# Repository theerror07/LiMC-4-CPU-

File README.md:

# LiMC-4-CPU-
All the documentation and information about my CPU project.

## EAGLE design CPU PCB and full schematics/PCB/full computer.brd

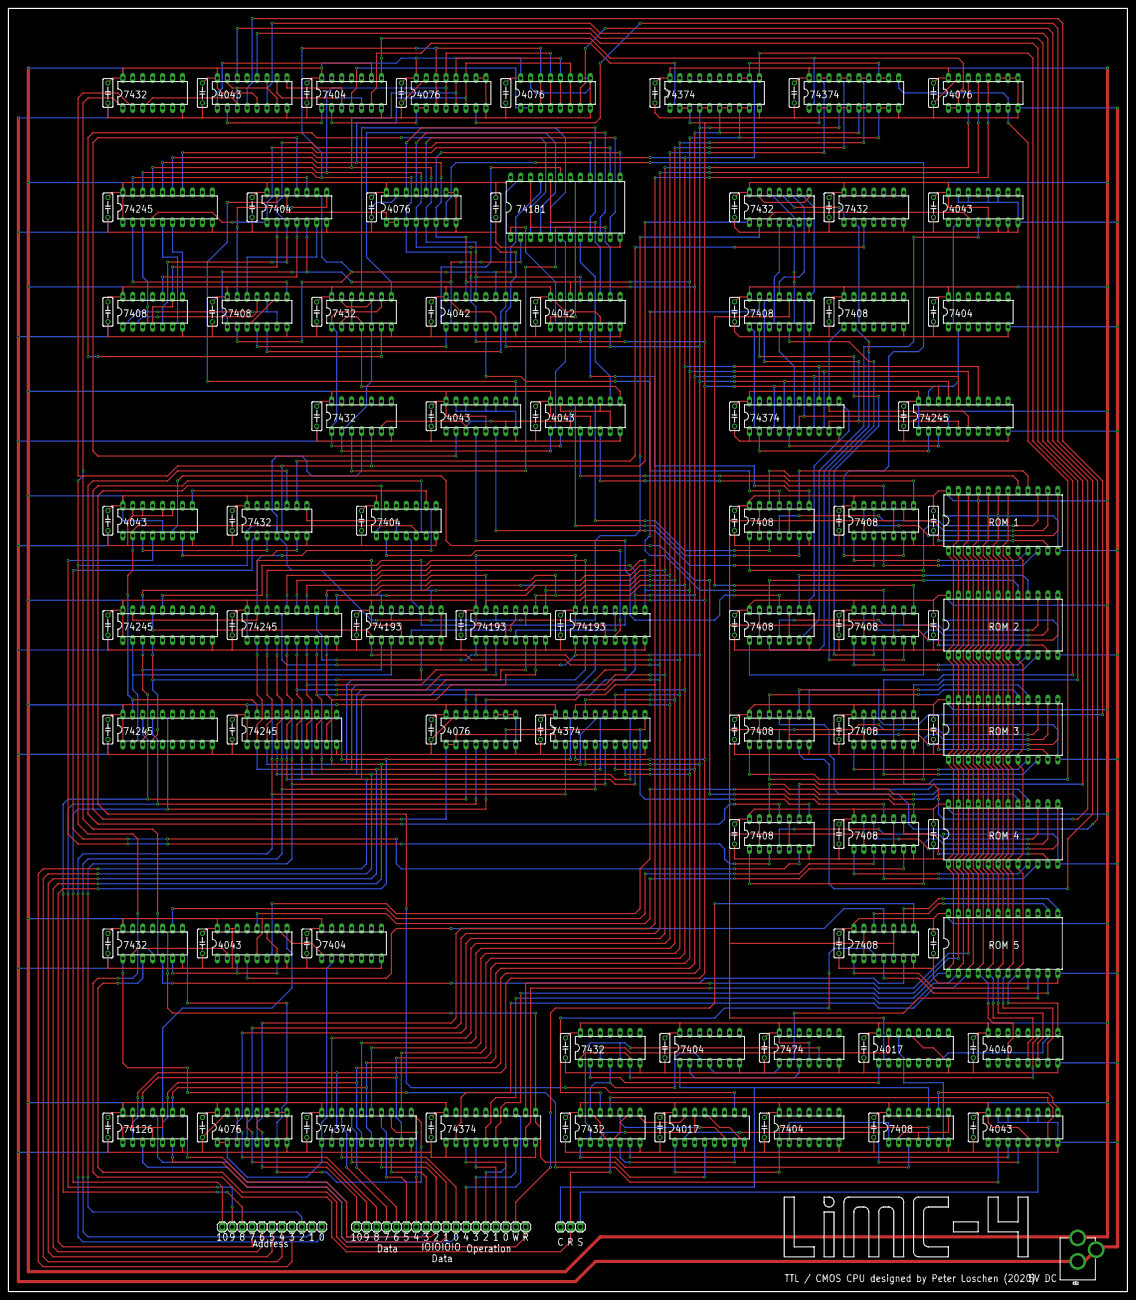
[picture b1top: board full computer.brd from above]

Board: 2 copper layers, 285.8 x 327.7 mm, 146 parts (0 on the bottom side), 244 nets.

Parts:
E$1, E$3, E$4, E$5, E$6, E$7, E$8, E$9, E$10, E$11, E$12, E$13, E$14, E$15, E$16, E$17, E$18, E$19, E$20, E$21, E$22, E$23, E$24, E$25, E$26, E$27, E$28, E$29, E$30, E$31, E$32, E$33, E$34, E$35, E$36, E$37, E$38, E$39, E$40, E$41, E$42, E$43, E$44, E$45, E$46, E$47, E$48, E$49, E$50, E$51, E$52, E$53, E$54, E$55, E$56, E$57, E$58, E$59, E$60, E$61, E$62, E$63, E$64, E$65, E$66, E$67, E$68, E$69, E$70, E$71, E$72: C050-025X075
E$2: POWER_JACK_PTH
IC1, IC7: 4017N; DIL16
IC2, IC27, IC34, IC48, IC49, IC56, IC61: 4043N; DIL16
IC3, IC8, IC26, IC40, IC44, IC45, IC55, IC59, IC62: 74LS32N; DIL14
IC4, IC16, IC17, IC18, IC19, IC20, IC21, IC22, IC23, IC24, IC51, IC52, IC53, IC54: 74ALS08N; DIL14
IC5, IC10, IC31, IC39, IC46, IC57, IC68: 74ALS04N; DIL14
IC6: 4040N; DIL16
IC9: 74LS74N; DIL14
IC11, IC12, IC13, IC14, IC15: 28C16AP; DIL24-6
IC25, IC38, IC50, IC63, IC64, IC67: 4076N; DIL16
IC28, IC29, IC37, IC60, IC65, IC66: 74LS374N; DIL20
IC30: 74LS126N; DIL14
IC32, IC33, IC35, IC36, IC47, IC58: 74LS245N; DIL20
IC41: 74S181N; DIL24-6
IC42, IC43: 4042N; DIL16
JP1: 1X03
JP2: 1X18
JP3: 1X11
V1, V2, V3: 74193N; DIL16

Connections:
ACCUMULATORLATCH: IC16.6, IC50.7
ACCUMULATOROUTPUT: IC16.3, IC49.6
ADDRESS0: IC35.18, IC37.2, JP3.1
ADDRESS1: IC35.17, IC37.5, JP3.2
ADDRESS2: IC35.16, IC37.6, JP3.3
ADDRESS3: IC35.15, IC37.9, JP3.4
ADDRESS4: IC35.14, IC37.12, JP3.5
ADDRESS5: IC35.13, IC37.15, JP3.6
ADDRESS6: IC35.12, IC37.16, JP3.7
ADDRESS7: IC35.11, IC37.19, JP3.8
ADDRESS8: IC36.18, IC38.3, JP3.9
ADDRESS9: IC36.17, IC38.4, JP3.10
ADDRESS10: IC36.16, IC38.5, JP3.11
ALUFLAGOUT: IC19.11, IC49.4
BUFFERTODATABUS: IC22.6, IC27.12
CUREAD: IC2.2, IC26.1
D0: IC28.3, IC30.3, JP2.8
D1: IC28.4, IC30.6, JP2.9
D2: IC28.7, IC30.8, JP2.10
D3: IC28.8, IC30.11, JP2.11
D4: IC28.13, JP2.12
D5: IC28.14, JP2.13
D6: IC28.17, JP2.14
D7: IC28.18, JP2.15
D8: IC25.14, JP2.16
D9: IC25.13, JP2.17
D10: IC25.12, JP2.18
DATABUS0: IC28.2, IC30.2, IC32.18, IC37.3, IC42.4, IC43.4, IC47.18, IC50.3, IC58.18, IC60.3, IC63.3, IC63.14, IC64.3, IC64.14, IC65.2, IC65.3, IC66.2, IC66.3, V1.15
DATABUS1: IC28.5, IC30.5, IC32.17, IC37.4, IC42.7, IC43.7, IC47.17, IC50.4, IC58.17, IC60.4, IC63.4, IC63.13, IC64.4, IC64.13, IC65.4, IC65.5, IC66.4, IC66.5, V1.1
DATABUS2: IC28.6, IC30.9, IC32.16, IC37.7, IC42.13, IC43.13, IC47.16, IC50.5, IC58.16, IC60.7, IC63.5, IC63.12, IC64.5, IC64.12, IC65.6, IC65.7, IC66.6, IC66.7, V1.10
DATABUS3: IC28.9, IC30.12, IC32.15, IC37.8, IC42.14, IC43.14, IC47.15, IC50.6, IC58.15, IC60.8, IC63.6, IC63.11, IC64.6, IC64.11, IC65.8, IC65.9, IC66.8, IC66.9, V1.9
DATABUS4: IC28.12, IC32.14, IC37.13, IC47.14, IC58.14, IC60.13, IC65.12, IC65.13, IC66.12, IC66.13, V2.15
DATABUS5: IC28.15, IC32.13, IC37.14, IC66.14, IC66.15, V2.1
DATABUS6: IC28.16, IC32.12, IC37.17, IC66.16, IC66.17, V2.10
DATABUS7: IC28.19, IC32.11, IC37.18, IC66.18, IC66.19, V2.9
DATABUS8: IC25.3, IC33.18, IC38.14, IC67.3, IC67.14, V3.15
DATABUS9: IC25.4, IC33.17, IC38.13, IC67.4, IC67.13, V3.1
DATABUS10: IC25.5, IC33.16, IC38.12, IC67.5, IC67.12, V3.10
DATABUSTORAM: IC22.8, IC27.6
DECODECLOCK: IC4.6, IC7.14
EEPROMOUT: IC7.2, IC16.2, IC16.5, IC16.10, IC16.13, IC17.2, IC17.5, IC17.10, IC17.13, IC18.2, IC18.5, IC18.10, IC18.13, IC19.2, IC19.5, IC19.10, IC19.13, IC20.2, IC20.5, IC20.10, IC20.13, IC21.2, IC21.5, IC21.10, IC21.13, IC22.2, IC22.5, IC22.10, IC22.13, IC23.2, IC23.5, IC23.10, IC23.13, IC24.2, IC24.5, IC24.10, IC24.13
EEPROMRESET: IC9.2, IC15.10
FLAGJSRLATCH: IC20.11, IC65.11
FLAGJSROUTPUT: IC20.8, IC61.12
FLAGLATCH: IC19.8, IC60.11
FLAGOUTPUT: IC19.6, IC56.4
FUNCTION0: IC17.6, IC48.14
FUNCTION1: IC17.3, IC48.12
FUNCTION2: IC16.11, IC48.6
FUNCTION3: IC16.8, IC48.4
GND: E$1.1, E$2.GND, E$2.GNDBREAK, E$3.1, E$4.1, E$5.1, E$6.1, E$7.1, E$8.1, E$9.1, E$10.1, E$11.1, E$12.1, E$13.1, E$14.1, E$15.1, E$16.1, E$17.1, E$18.1, E$19.1, E$20.1, E$21.1, E$22.1, E$23.1, E$24.1, E$25.1, E$26.1, E$27.1, E$28.1, E$29.1, E$30.1, E$31.1, E$32.1, E$33.1, E$34.1, E$35.1, E$36.1, E$37.1, E$38.1, E$39.1, E$40.1, E$41.1, E$42.1, E$43.1, E$44.1, E$45.1, E$46.1, E$47.1, E$48.1, E$49.1, E$50.1, E$51.1, E$52.1, E$53.1, E$54.1, E$55.1, E$56.1, E$57.1, E$58.1, E$59.1, E$60.1, E$61.1, E$62.1, E$63.1, E$64.1, E$65.1, E$66.1, E$67.1, E$68.1, E$69.1, E$70.1, E$71.1, E$72.1, IC1.8, IC1.13, IC2.8, IC2.11, IC2.12, IC2.14, IC2.15, IC3.7, IC4.7, IC5.7, IC6.8, IC7.8, IC7.13, IC8.7, IC9.7, IC10.7, IC11.12, IC11.18, IC11.19, IC11.20, IC12.12, IC12.18, IC12.19, IC12.20, IC13.12, IC13.18, IC13.19, IC13.20, IC14.12, IC14.18, IC14.19, IC14.20, IC15.12, IC15.18, IC15.19, IC15.20, IC16.7, IC17.7, IC18.7, IC19.7, IC20.7, IC21.7, IC22.7, IC23.7, IC24.7, IC25.8, IC25.9, IC25.10, IC25.11, IC25.15, IC26.7, IC27.8, IC27.14, IC27.15, IC28.10, IC29.1, IC29.10, IC30.7, IC31.7, IC32.10, IC33.10, IC34.8, IC34.11, IC34.12, IC34.14, IC34.15, IC35.10, IC36.10, IC37.10, IC38.8, IC38.9, IC38.10, IC38.11, IC38.15, IC39.7, IC40.7, IC41.12, IC42.8, IC43.8, IC44.7, IC45.7, IC46.7, IC47.10, IC48.8, IC49.8, IC49.11, IC49.12, IC49.14, IC49.15, IC50.8, IC50.9, IC50.10, IC50.15, IC51.7, IC52.7, IC53.7, IC54.7, IC55.7, IC56.6, IC56.7, IC56.8, IC56.11, IC56.12, IC56.14, IC56.15, IC57.7, IC58.10, IC59.7, IC60.1, IC60.10, IC61.8, IC62.7, IC63.8, IC63.9, IC63.10, IC63.15, IC64.8, IC64.9, IC64.10, IC64.15, IC65.10, IC66.10, IC67.8, IC67.9, IC67.10, IC67.11, IC67.15, IC68.7, V1.8, V2.8, V3.8, V3.9
IOLATCH: IC1.4, IC26.10, IC29.11
LATCHRESET: IC24.6, IC26.5, IC40.5, IC45.5, IC55.1, IC62.2
MICROCODELATCH: IC22.3, IC26.9
MICROCODERAMREAD: IC24.11, IC27.4
unnamed: V1.12, V2.5
unnamed: IC1.2, IC2.4
unnamed: IC2.3, IC3.6
unnamed: V2.12, V3.5
unnamed: IC1.7, IC3.5
unnamed: IC1.1, IC4.5, IC5.1
unnamed: IC4.1, IC5.2
unnamed: IC3.1, IC4.3
unnamed: IC1.14, IC3.3
unnamed: IC39.4, V1.11, V2.11, V3.11
unnamed: IC39.3, IC40.8
unnamed: IC41.2, IC42.2, IC46.5, IC51.1
unnamed: IC41.23, IC42.10, IC51.5
unnamed: IC1.15, IC3.8
unnamed: IC34.3, IC40.3
unnamed: IC41.19, IC42.1, IC51.4
unnamed: IC1.6, IC3.10
unnamed: IC6.10, IC7.7
unnamed: IC2.7, IC3.11
unnamed: IC34.2, IC35.19, IC36.19, IC39.5
unnamed: IC4.2, IC4.4, IC4.8
unnamed: IC41.22, IC43.10
unnamed: IC2.9, IC4.9
unnamed: IC41.20, IC43.11
unnamed: IC41.18, IC43.1
unnamed: IC41.1, IC43.2
unnamed: IC7.1, IC8.2
unnamed: IC7.15, IC8.3
unnamed: IC6.11, IC8.1, IC8.6
unnamed: IC26.6, IC27.3, IC27.7, IC27.11
unnamed: IC44.2, IC44.4, IC48.9
unnamed: IC26.2, IC27.2
unnamed: IC44.3, IC44.12
unnamed: IC41.5, IC44.11
unnamed: IC9.3, IC10.2
unnamed: IC44.1, IC44.9, IC45.1, IC48.2
unnamed: IC27.9, IC30.1, IC30.4, IC30.10, IC30.13
unnamed: IC9.1, IC10.4
unnamed: IC11.9, IC16.1
unnamed: IC11.10, IC16.4
unnamed: IC11.11, IC16.9
unnamed: IC11.13, IC16.12
unnamed: IC11.14, IC17.1
unnamed: IC11.15, IC17.4
unnamed: IC11.16, IC17.9
unnamed: IC11.17, IC17.12
unnamed: IC32.2, IC35.2, V1.3
unnamed: IC12.9, IC18.1
unnamed: IC12.10, IC18.4
unnamed: IC12.11, IC18.9
unnamed: IC12.13, IC18.12
unnamed: IC12.14, IC19.1
unnamed: IC12.15, IC19.4
unnamed: IC12.16, IC19.9
unnamed: IC12.17, IC19.12
unnamed: IC13.9, IC20.1
unnamed: IC13.10, IC20.4
unnamed: IC13.11, IC20.9
unnamed: IC13.13, IC20.12
unnamed: IC13.14, IC21.1
unnamed: IC13.15, IC21.4
unnamed: IC13.16, IC21.9
unnamed: IC13.17, IC21.12
unnamed: IC14.9, IC22.1
unnamed: IC14.10, IC22.4
unnamed: IC14.11, IC22.9
unnamed: IC14.13, IC22.12
unnamed: IC14.14, IC23.1
unnamed: IC14.15, IC23.4
unnamed: IC14.16, IC23.9
unnamed: IC14.17, IC23.12
unnamed: IC15.9, IC24.1
unnamed: IC15.11, IC24.4
unnamed: IC15.13, IC24.9
unnamed: IC15.14, IC24.12
unnamed: IC32.3, IC35.3, V1.2
unnamed: IC32.5, IC35.5, V1.7
unnamed: IC27.10, IC31.1
unnamed: IC32.6, IC35.6, V2.3
unnamed: IC32.7, IC35.7, V2.2
unnamed: IC32.8, IC35.8, V2.6
unnamed: IC33.2, IC36.2, V3.3
unnamed: IC33.3, IC36.3, V3.2
unnamed: IC33.4, IC36.4, V3.6
unnamed: IC41.3, IC44.6
unnamed: IC41.6, IC44.5, IC44.10, IC44.13, IC45.2, IC48.1
unnamed: IC34.7, IC40.6
unnamed: IC41.4, IC44.8
unnamed: IC34.9, IC39.9
unnamed: IC32.19, IC33.19, IC39.8
unnamed: IC32.4, IC35.4, V1.6
unnamed: IC41.8, IC48.10
unnamed: IC41.7, IC45.3
unnamed: IC41.9, IC50.14
unnamed: IC41.10, IC50.13
unnamed: IC25.7, IC26.8, IC28.11
unnamed: IC25.1, IC25.2, IC28.1, IC31.2
unnamed: IC41.11, IC50.12
unnamed: IC41.13, IC50.11
unnamed: IC53.1, IC58.2, IC60.2
unnamed: IC41.16, IC46.3, IC52.5
unnamed: IC46.4, IC52.10
unnamed: IC41.14, IC46.1, IC47.4
unnamed: IC46.2, IC52.4, IC52.9
unnamed: IC51.3, IC51.9
unnamed: IC51.6, IC51.10, IC52.1
unnamed: IC41.21, IC42.11, IC46.9, IC51.2
unnamed: IC46.8, IC51.13
unnamed: IC46.6, IC51.12
unnamed: IC51.11, IC52.2
unnamed: IC47.3, IC52.3
unnamed: IC47.2, IC51.8
unnamed: IC47.5, IC52.6
unnamed: IC47.6, IC52.8
unnamed: IC32.9, IC35.9, V2.7
unnamed: IC37.1, IC38.1, IC38.2, IC39.6
unnamed: IC46.10, IC47.19
unnamed: IC39.2, V1.5
unnamed: IC46.11, IC49.2
unnamed: IC46.13, IC49.9
unnamed: IC53.4, IC58.3, IC60.5
unnamed: IC53.9, IC58.4, IC60.6
unnamed: IC53.12, IC58.5, IC60.9
unnamed: IC54.1, IC58.6, IC60.12
unnamed: IC45.6, IC48.3, IC48.7, IC48.11, IC48.15, IC49.3, IC49.7
unnamed: IC46.12, IC50.1, IC50.2
unnamed: IC55.3, IC56.3
unnamed: IC61.1, IC68.9
unnamed: IC56.2, IC57.1
unnamed: IC57.2, IC58.19
unnamed: IC61.3, IC61.7, IC61.11, IC61.15, IC62.3
unnamed: IC61.2, IC68.1
unnamed: IC53.3, IC55.4
unnamed: IC53.6, IC55.5
unnamed: IC53.8, IC55.9
unnamed: IC53.11, IC55.10
unnamed: IC55.6, IC55.12
unnamed: IC55.8, IC55.13
unnamed: IC55.11, IC59.1
unnamed: IC54.3, IC59.2
unnamed: IC61.9, IC68.3
unnamed: IC61.10, IC68.5
unnamed: IC63.1, IC63.2, IC68.2
unnamed: IC64.1, IC64.2, IC68.4
unnamed: IC65.1, IC68.6
unnamed: IC66.1, IC67.1, IC67.2, IC68.8
OP0: IC29.3, JP2.3
OP1: IC29.4, JP2.4
OP2: IC29.7, JP2.5
OP3: IC29.8, JP2.6
OP4: IC29.13, JP2.7
OPCOUNTER0: IC6.9, IC11.8, IC12.8, IC13.8, IC14.8, IC15.8
OPCOUNTER1: IC6.7, IC11.7, IC12.7, IC13.7, IC14.7, IC15.7
OPCOUNTER2: IC6.6, IC11.6, IC12.6, IC13.6, IC14.6, IC15.6
OPCOUNTER3: IC6.5, IC11.5, IC12.5, IC13.5, IC14.5, IC15.5
OPCOUNTER4: IC6.3, IC11.4, IC12.4, IC13.4, IC14.4, IC15.4
OPERATIONDONE: IC3.2, IC8.5, IC9.5
OPREGISTER0: IC11.3, IC12.3, IC13.3, IC14.3, IC15.3, IC29.2
OPREGISTER1: IC11.2, IC12.2, IC13.2, IC14.2, IC15.2, IC29.5
OPREGISTER2: IC11.1, IC12.1, IC13.1, IC14.1, IC15.1, IC29.6
OPREGISTER3: IC11.23, IC12.23, IC13.23, IC14.23, IC15.23, IC29.9
OPREGISTER4: IC11.22, IC12.22, IC13.22, IC14.22, IC15.22, IC29.12
OVERFLOW: IC18.6, IC53.5
PC1ACTIVE: IC23.6, IC40.2
PC1FLAGLATCH: IC40.9, IC59.3
PC1LATCH: IC23.11, IC40.10
PC1TODATABUS: IC22.11, IC34.6
PC2ACTIVE: IC23.3, IC34.4
PC2LATCH: IC23.8, IC37.11, IC38.7
PCINC: IC1.10, IC39.1
PCJSRLATCH: IC20.6, IC66.11, IC67.7
PCJSROUTPUT: IC20.3, IC61.14
RAMREAD: IC26.3, JP2.1
RAMWRITE: IC24.8, JP2.2
START: IC2.6, JP1.1
STOP: IC3.12, IC24.3
SYSTEMCLOCK: IC4.10, IC10.1, JP1.3
SYSTEMRESET: IC3.4, IC3.9, IC3.13, IC8.4, IC10.3, IC26.4, IC40.1, IC40.4, IC45.4, IC55.2, IC62.1, JP1.2, V1.14, V2.14, V3.14
UNDERFLOW: IC18.3, IC53.2
VCC: E$1.2, E$2.PWR, E$3.2, E$4.2, E$5.2, E$6.2, E$7.2, E$8.2, E$9.2, E$10.2, E$11.2, E$12.2, E$13.2, E$14.2, E$15.2, E$16.2, E$17.2, E$18.2, E$19.2, E$20.2, E$21.2, E$22.2, E$23.2, E$24.2, E$25.2, E$26.2, E$27.2, E$28.2, E$29.2, E$30.2, E$31.2, E$32.2, E$33.2, E$34.2, E$35.2, E$36.2, E$37.2, E$38.2, E$39.2, E$40.2, E$41.2, E$42.2, E$43.2, E$44.2, E$45.2, E$46.2, E$47.2, E$48.2, E$49.2, E$50.2, E$51.2, E$52.2, E$53.2, E$54.2, E$55.2, E$56.2, E$57.2, E$58.2, E$59.2, E$60.2, E$61.2, E$62.2, E$63.2, E$64.2, E$65.2, E$66.2, E$67.2, E$68.2, E$69.2, E$70.2, E$71.2, E$72.2, IC1.16, IC2.5, IC2.16, IC3.14, IC4.14, IC5.14, IC6.16, IC7.16, IC8.14, IC9.4, IC9.14, IC10.14, IC11.21, IC11.24, IC12.21, IC12.24, IC13.21, IC13.24, IC14.21, IC14.24, IC15.21, IC15.24, IC16.14, IC17.14, IC18.14, IC19.14, IC20.14, IC21.14, IC22.14, IC23.14, IC24.14, IC25.16, IC26.14, IC27.5, IC27.16, IC28.20, IC29.20, IC30.14, IC31.14, IC32.1, IC32.20, IC33.1, IC33.20, IC34.5, IC34.16, IC35.1, IC35.20, IC36.1, IC36.20, IC37.20, IC38.16, IC39.14, IC40.14, IC41.24, IC42.6, IC42.16, IC43.6, IC43.16, IC44.14, IC45.14, IC46.14, IC47.1, IC47.20, IC48.5, IC48.16, IC49.5, IC49.16, IC50.16, IC51.14, IC52.14, IC53.14, IC54.14, IC55.14, IC56.5, IC56.16, IC57.14, IC58.1, IC58.20, IC59.14, IC60.20, IC61.5, IC61.16, IC62.14, IC63.16, IC64.16, IC65.20, IC66.20, IC67.16, IC68.14, V1.4, V1.16, V2.4, V2.16, V3.4, V3.16
X<Y: IC18.11, IC53.13
X=Y: IC18.8, IC53.10
X>Y: IC19.3, IC54.2
XJSRLATCH: IC21.11, IC63.7
XJSROUTPUT: IC21.8, IC61.4
XLATCH: IC17.11, IC42.5
YJSRLATCH: IC21.6, IC64.7
YJSROUTPUT: IC21.3, IC61.6
YLATCH: IC17.8, IC43.5

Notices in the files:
parts and their libraries:
SparkFun-Connectors: Licensing: Creative Commons ShareAlike 4.0 International - https://creativecommons.org/licenses/by-sa/4.0
